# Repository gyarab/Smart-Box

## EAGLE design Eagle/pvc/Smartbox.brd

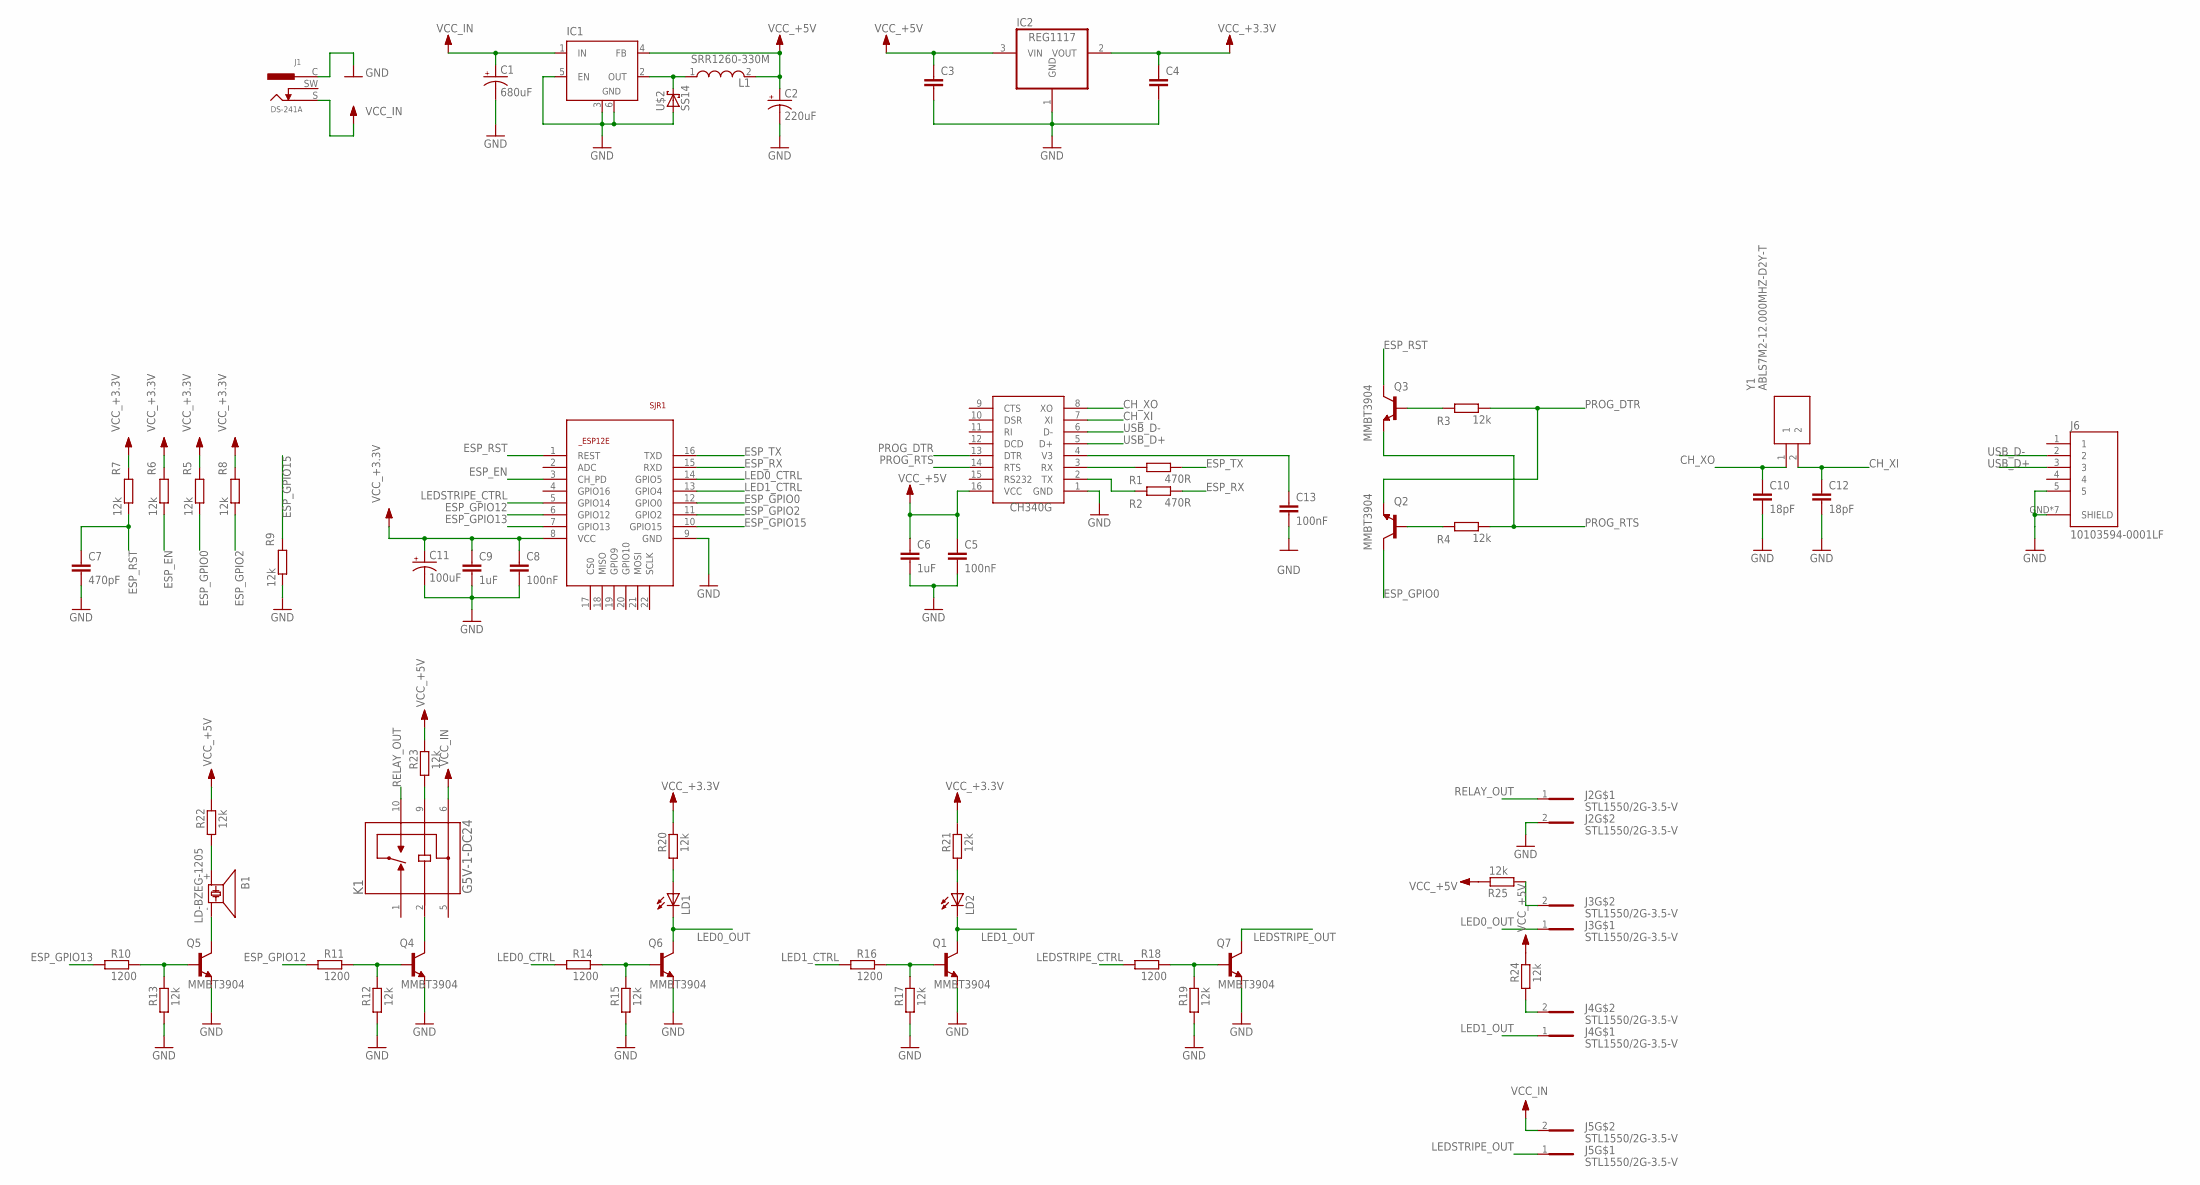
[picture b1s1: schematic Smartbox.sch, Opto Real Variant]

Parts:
B1: LD-BZEG-1205; LD-BZEG-12XX
C1: 680uF; PANASONIC_D
C2: 220uF; PANASONIC_D
C3, C4: C-EUC0805; C0805
C5, C8, C13: 100nF; C0805
C6, C9: 1uF; C0805
C7: 470pF; C0805
C10, C12: 18pF; C0805
C11: 100uF; PANASONIC_D
IC1: LM2596S; TO263-5
IC2: REG1117; SOT223
J1: DS-241A; DS-241
J2, J3, J4, J5: STL1550/2G-3.5-V; STL1550/2G-3.5-V-GREEN
J6: 10103594-0001LF
K1: G5V-1-DC24
L1: SRR1260-330M; SRR1260-150M
LD1, LD2: LEDCHIPLED_0805; CHIPLED_0805
Q1, Q2, Q3, Q4, Q5, Q6, Q7: MMBT3904; SOT23
R1, R2: 470R; R0805
R3, R4, R5, R6, R7, R8, R9, R12, R13, R15, R17, R19, R20, R21, R22, R23, R24, R25: 12k; R0805
R10, R11, R14, R16, R18: 1200; R0805
SJR1: ESP8266-12EESP12E; ESP8266-ESP12E
U$2: SS14; DO-214AC
U$3: CH340G; SOIC16
Y1: ABLS7M2-12.000MHZ-D2Y-T; ABLS7M216000MHZD2YT

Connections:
CH_XI: C12.1, U$3.7 (XI), Y1.2
CH_XO: C10.1, U$3.8 (XO), Y1.1
ESP_EN: R6.2, SJR1.3 (CH_PD)
ESP_GPIO0: Q2.3 (C), R5.2, SJR1.12 (GPIO0)
ESP_GPIO2: R8.2, SJR1.11 (GPIO2)
ESP_GPIO12: R11.1, SJR1.6 (GPIO12)
ESP_GPIO13: R10.1, SJR1.7 (GPIO13)
ESP_GPIO15: R9.1, SJR1.10 (GPIO15)
ESP_RST: C7.1, Q3.3 (C), R7.2, SJR1.1 (REST)
ESP_RX: R2.2, SJR1.15 (RXD)
ESP_TX: R1.2, SJR1.16 (TXD)
GND: C1.-, C2.-, C3.2, C4.2, C5.2, C6.2, C7.2, C8.2, C9.2, C10.2, C11.-, C12.2, C13.1, IC1.3 (GND), IC1.5 (EN), IC1.6 (GND), IC2.1 (GND), J1.C, J2.2, J6.5, J6.GND (SHIELD), J6.GND$1 (SHIELD), J6.GND$2 (SHIELD), J6.S1 (SHIELD), J6.S2 (SHIELD), J6.S3 (SHIELD), J6.S4 (SHIELD), Q1.2 (E), Q4.2 (E), Q5.2 (E), Q6.2 (E), Q7.2 (E), R9.2, R12.1, R13.1, R15.1, R17.1, R19.1, SJR1.9 (GND), U$2.A, U$3.1 (GND)
LED0_CTRL: R14.1, SJR1.14 (GPIO5)
LED0_OUT: J3.1, LD1.C, Q6.3 (C)
LED1_CTRL: R16.1, SJR1.13 (GPIO4)
LED1_OUT: J4.1, LD2.C, Q1.3 (C)
LEDSTRIPE_CTRL: R18.1, SJR1.5 (GPIO14)
LEDSTRIPE_OUT: J5.1, Q7.3 (C)
unnamed: C13.2, U$3.4 (V3)
unnamed: R1.1, U$3.3 (RX)
unnamed: K1.2, Q4.3 (C)
unnamed: Q5.1 (B), R10.2, R13.2
unnamed: B1.-, Q5.3 (C)
unnamed: Q1.1 (B), R16.2, R17.2
unnamed: Q4.1 (B), R11.2, R12.2
unnamed: Q6.1 (B), R14.2, R15.2
unnamed: Q7.1 (B), R18.2, R19.2
unnamed: LD1.A, R20.1
unnamed: LD2.A, R21.1
unnamed: B1.+, R22.1
unnamed: K1.9, R23.1
unnamed: J4.2, R24.1
unnamed: J3.2, R25.1
unnamed: R2.1, U$3.2 (TX)
unnamed: Q2.1 (B), R4.1
unnamed: Q3.1 (B), R3.1
unnamed: IC1.2 (OUT), L1.1, U$2.C
PROG_DTR: Q2.2 (E), R3.2, U$3.13 (DTR)
PROG_RTS: Q3.2 (E), R4.2, U$3.14 (RTS)
RELAY_OUT: J2.1, K1.10
USB_D+: J6.3, U$3.5 (D+)
USB_D-: J6.2, U$3.6 (D-)
VCC_+3.3V: C4.1, C8.1, C9.1, C11.+, IC2.2 (VOUT), R5.1, R6.1, R7.1, R8.1, R20.2, R21.2, SJR1.8 (VCC)
VCC_+5V: C2.+, C3.1, C5.1, C6.1, IC1.4 (FB), IC2.3 (VIN), L1.2, R22.2, R23.2, R24.2, R25.2, U$3.16 (VCC)
VCC_IN: C1.+, IC1.1 (IN), J1.S, J5.2, K1.6

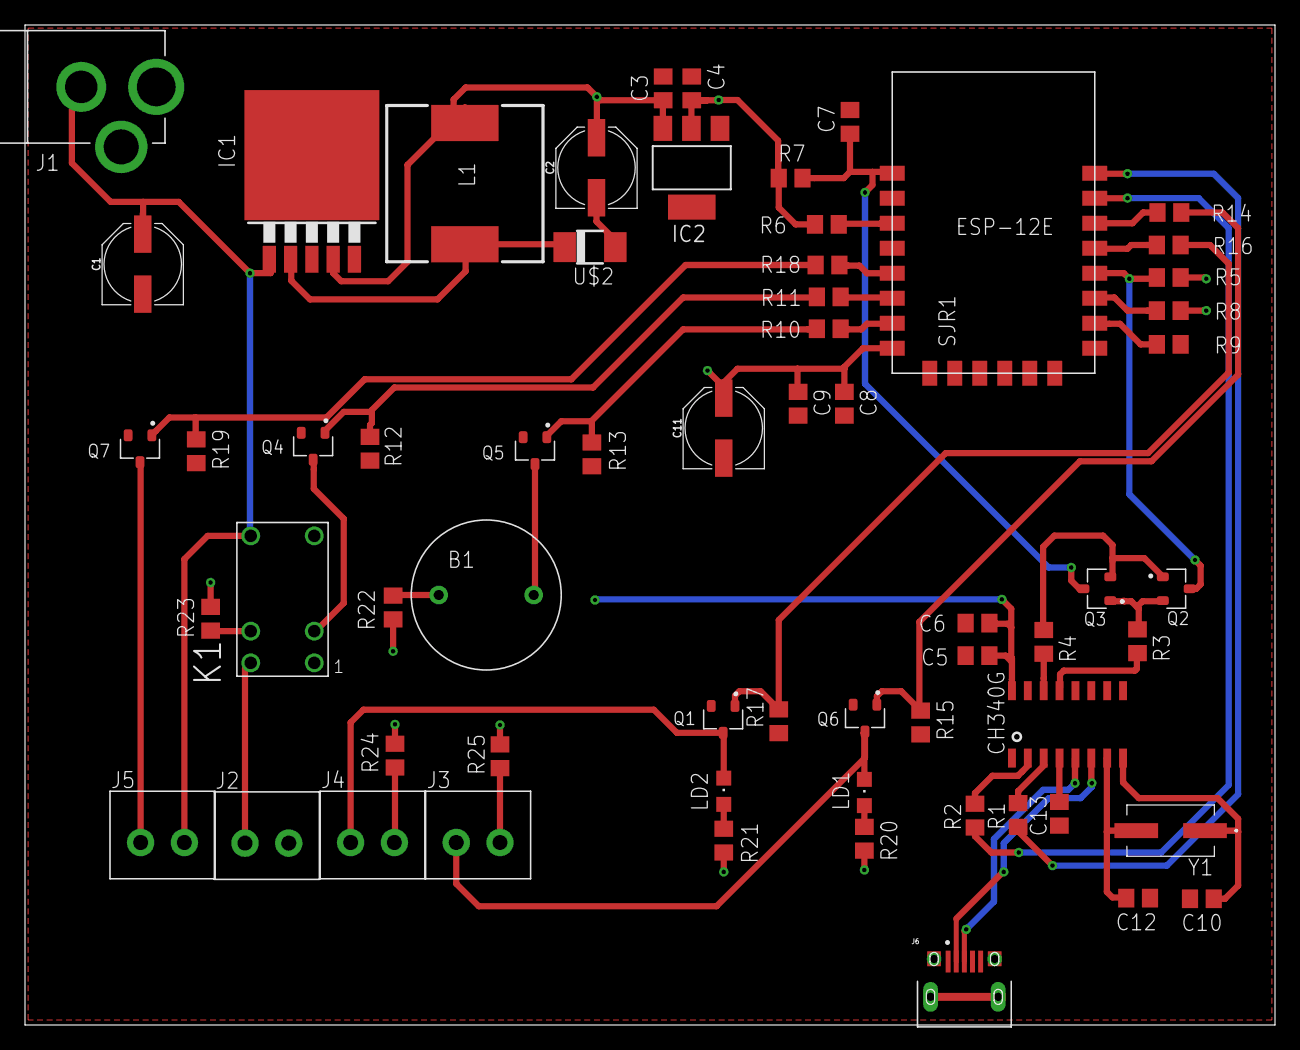
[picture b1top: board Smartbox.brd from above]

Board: 2 copper layers, 100.0 x 80.0 mm, 62 parts (0 on the bottom side), 45 nets.

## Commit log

2020-02-11 Add Procfile and requirements.txt
2020-02-11 Change setting.py
2020-02-11 Change Procfile
2020-02-17 Add lock and unlock functions
2020-02-18 Get locked status
2020-02-24 Add authentification
2020-02-24 Add djoser to requirements.txt
2020-03-01 Náprava
2020-03-01 Náprava 2
2020-03-01 offline mode
2020-03-01 Smartbox app recovery
2020-03-02 Prvni cast dokumentace
2020-03-03 Add files via upload
    dokumentace
2020-03-03 dokumentace
2020-03-03 update repo
2020-03-03 app update
2020-03-03 uprava dokumentace
2020-03-04 ArduinoCode V2
2020-03-05 Aktualizace kodu
2020-04-14 bug fixes
2020-04-14 bux fixes: list indexing
2020-04-15 progress indicator
2020-04-19 app logo
2020-04-29 API a Eagle
2020-04-29 Eagle
2020-04-29 Add files via upload
    uprava dokumentace
2020-04-29 dokumentace pre-final
2020-04-30 fotodokumentace + úpravy v dokumentaci
2020-05-06 odstraneni externich knihoven
2020-05-19 poster
2020-06-05 Bump django from 3.0.3 to 3.0.7 in /DjangoAPI/smartboxrestapi
    Bumps [django](https://github.com/django/django) from 3.0.3 to 3.0.7.
    - [Release notes](https://github.com/django/django/releases)
    - [Commits](https://github.com/django/django/compare/3.0.3...3.0.7)
2021-03-19 Bump django from 3.0.3 to 3.1.6 in /DjangoAPI/smartboxrestapi
    Bumps [django](https://github.com/django/django) from 3.0.3 to 3.1.6.
    - [Release notes](https://github.com/django/django/releases)
    - [Commits](https://github.com/django/django/compare/3.0.3...3.1.6)
2021-03-19 Bump djangorestframework in /DjangoAPI/smartboxrestapi
    Bumps [djangorestframework](https://github.com/encode/django-rest-framework) from 3.11.0 to 3.11.2.
    - [Release notes](https://github.com/encode/django-rest-framework/releases)
    - [Commits](https://github.com/encode/django-rest-framework/compare/3.11.0...3.11.2)
2021-03-30 Bump django from 3.0.3 to 3.0.12 in /DjangoAPI/smartboxrestapi
    Bumps [django](https://github.com/django/django) from 3.0.3 to 3.0.12.
    - [Release notes](https://github.com/django/django/releases)
    - [Commits](https://github.com/django/django/compare/3.0.3...3.0.12)
2021-04-08 Bump django from 3.0.3 to 3.0.14 in /DjangoAPI/smartboxrestapi
    Bumps [django](https://github.com/django/django) from 3.0.3 to 3.0.14.
    - [Release notes](https://github.com/django/django/releases)
    - [Commits](https://github.com/django/django/compare/3.0.3...3.0.14)
2021-06-04 Bump django from 3.0.3 to 3.1.9 in /DjangoAPI/smartboxrestapi
    Bumps [django](https://github.com/django/django) from 3.0.3 to 3.1.9.
    - [Release notes](https://github.com/django/django/releases)
    - [Commits](https://github.com/django/django/compare/3.0.3...3.1.9)
    ---
    updated-dependencies:
    - dependency-name: django
2021-06-10 Bump django from 3.0.3 to 3.1.12 in /DjangoAPI/smartboxrestapi
    Bumps [django](https://github.com/django/django) from 3.0.3 to 3.1.12.
    - [Release notes](https://github.com/django/django/releases)
    - [Commits](https://github.com/django/django/compare/3.0.3...3.1.12)
    ---
    updated-dependencies:
    - dependency-name: django
2021-09-22 Bump django from 3.0.3 to 3.1.13 in /DjangoAPI/smartboxrestapi
    Bumps [django](https://github.com/django/django) from 3.0.3 to 3.1.13.
    - [Release notes](https://github.com/django/django/releases)
    - [Commits](https://github.com/django/django/compare/3.0.3...3.1.13)
    ---
    updated-dependencies:
    - dependency-name: django

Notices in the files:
parts and their libraries:
SparkFun-Capacitors: Licensing: Creative Commons ShareAlike 4.0 International - https://creativecommons.org/licenses/by-sa/4.0
